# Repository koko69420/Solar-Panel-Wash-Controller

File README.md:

# Solar Panel Wash Controller

An automated, hardware-timed electronic controller PCB designed to schedule and actuate solar panel washing cycles to mitigate dust accumulation, soiling losses, and photovoltaic efficiency degradation.

Designed in KiCad with integrated Real-Time Clock (RTC) scheduling, high-current pump relay/driver stages, and industrial terminal interfaces.

---

## Features

- **Automated Cleaning Schedule**:
  - Precision timekeeping via dedicated I2C Real-Time Clock (RTC) module (DS3231/DS1307 battery-backed) for reliable daily or weekly dawn/dusk wash cycles.
- **Robust Pump & Solenoid Drive Stage**:
  - High-current relay and switching stage engineered to drive 12V/24V high-pressure water booster pumps and solenoid valves.
  - Flyback diode suppression and optocoupled logic isolation to prevent inductive transient resets.
- **Aesthetic Rounded-Track PCB Design**:
  - Custom PCB routing featuring smooth curved/teardrop trace geometry for improved signal integrity and solder-mask resilience.
  - Multi-layer power routing with broad copper pours to handle high inrush pump currents.
- **Modular Sub-System Layout**:
  - Dedicated sub-module architecture separating the low-voltage control/logic plane from the high-voltage actuator switching plane.

---

## Hardware Specification

- **RTC Module**: I2C Real-Time Clock with CR2032 backup battery holder (`RTC Module.kicad_sym`).
- **Control Interface**: Multi-pin microcontroller interface header with analog and digital telemetry pins.
- **Output Actuators**: SPDT Power Relays / High-Side Power Switching stages.
- **PCB Stackup**: 2-layer FR4 (1.6 mm core, 1 oz copper).
- **Renders & Manufacturing**:
  - 3D photorealistic board renders: `Front.png` and `Back.png`.
  - Manufacturing schematic: `Schematic.pdf` / `Schematic.png`.

---

## Hardware Renders & Schematic

### 3D Photorealistic PCB Views

| Top View | Bottom View |
| :---: | :---: |
|  |  |

### Electrical Schematic

---

## Project Structure

```text
Solar-Panel-Wash-Controller/
├── Front.png                         # 3D PCB front render
├── Back.png                          # 3D PCB back render
├── Schematic.pdf                     # Complete schematic documentation
├── Solar_pannel_wash_controller.kicad_sch # Main KiCad schematic
├── Solar_pannel_wash_controller.kicad_pcb # Main KiCad PCB layout
├── Solar_pannel_wash_controller.kicad_pro # KiCad project configuration
├── RTC Module.kicad_sym              # Custom RTC schematic symbol
├── Solar_pannel_wash_controller_sub-modules/ # Modular breakout & rounded PCB files
│   ├── Solar_pannel_wash_controller_sub-modules.kicad_sch
│   ├── Solar_pannel_wash_controller_sub-modules.kicad_pcb
│   └── Solar_pannel_wash_controller_sub-modules-rounded.kicad_pcb
├── .gitignore                        # Git ignore rules
└── README.md                         # Project documentation
```

---

## EDA & Design Files

Designed using **KiCad 7 / 8**:
- Open `Solar_pannel_wash_controller.kicad_pro` to inspect or modify the full system schematic and board layout.
- Review `Schematic.pdf` for circuit wiring, power distribution networks, and connector assignments.

---

## License

Hardware design. All rights reserved by the author.

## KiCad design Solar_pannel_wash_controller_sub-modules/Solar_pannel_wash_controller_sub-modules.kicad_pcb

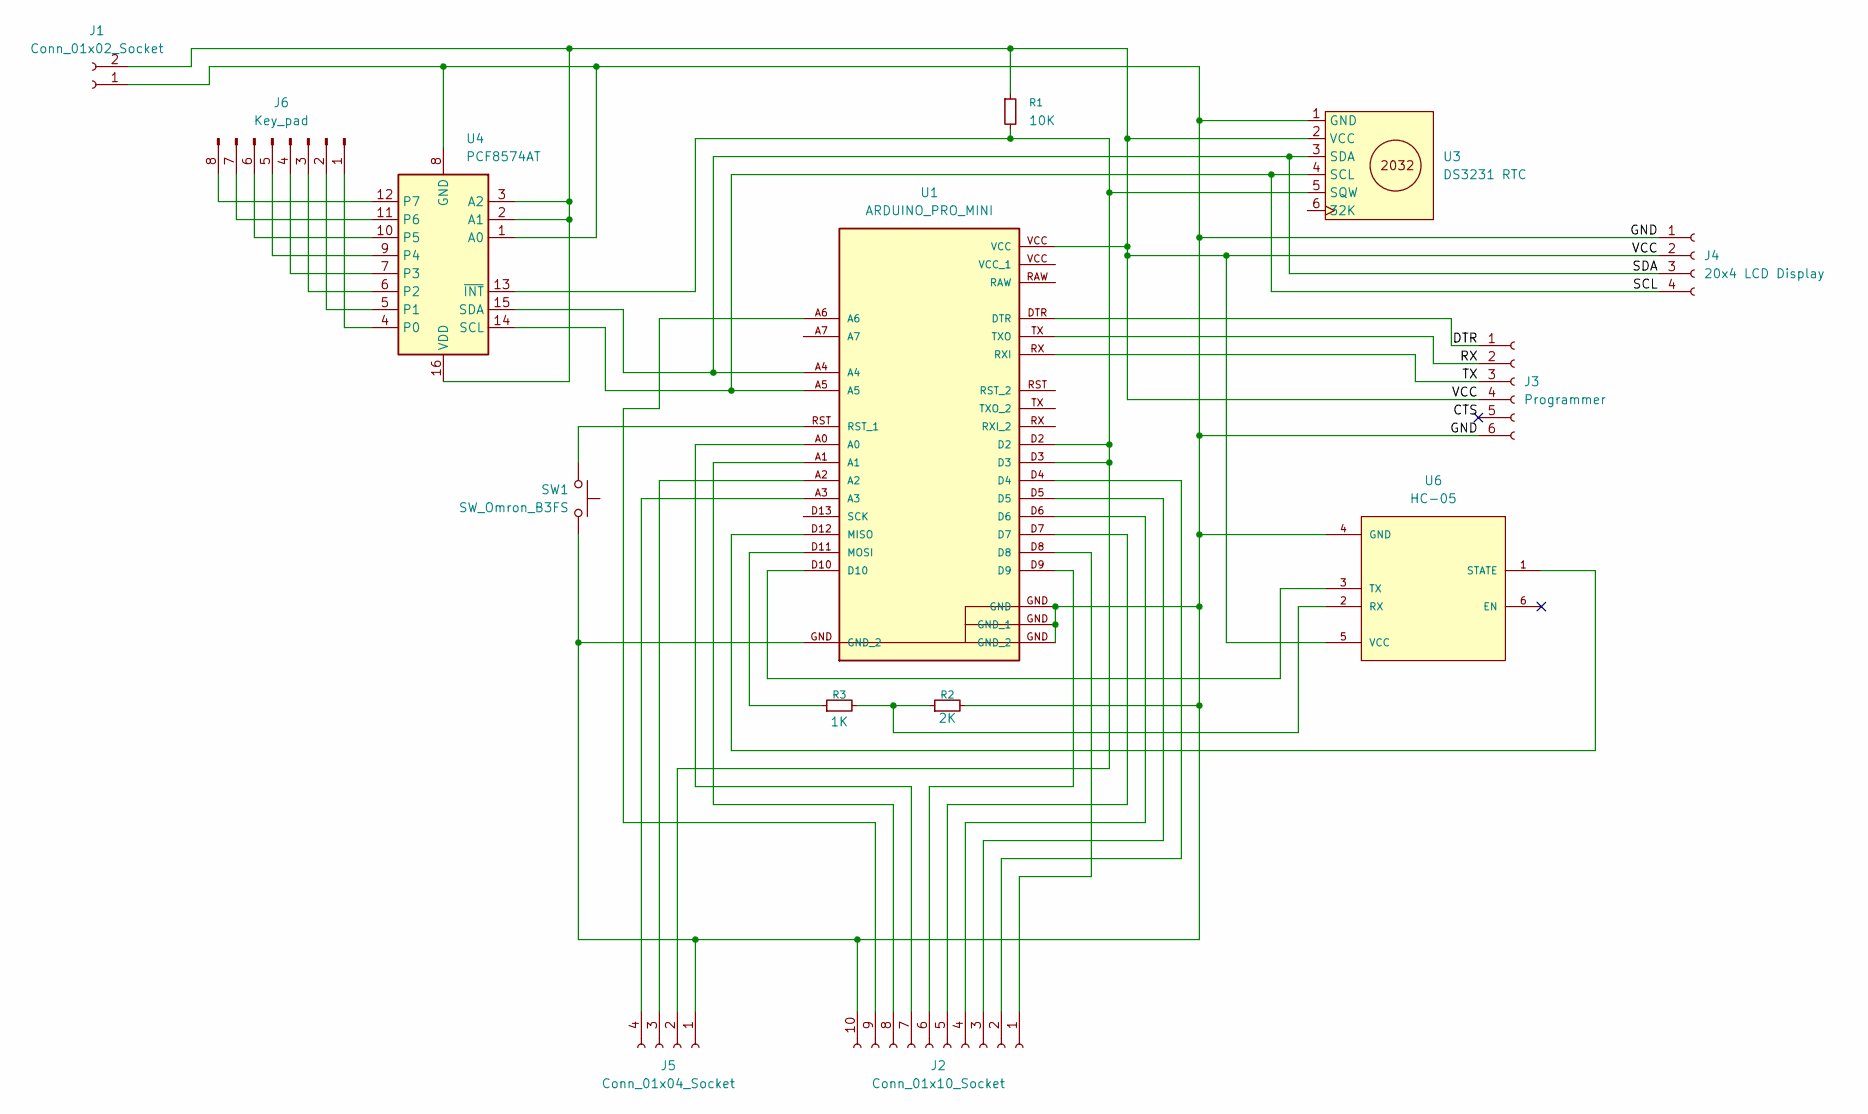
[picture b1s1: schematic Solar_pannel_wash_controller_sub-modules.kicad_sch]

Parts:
J1: Conn_01x02_Socket; JST_XH_B2B-XH-A_1x02_P2.50mm_Vertical
J2: Conn_01x10_Socket; JST_XH_B10B-XH-A_1x10_P2.50mm_Vertical
J3: Programmer; PinSocket_1x06_P2.54mm_Horizontal
J4: 20x4 LCD Display; JST_XH_B4B-XH-A_1x04_P2.50mm_Vertical
J5: Conn_01x04_Socket; JST_XH_B4B-XH-A_1x04_P2.50mm_Vertical
J6: Key_pad; PinHeader_1x08_P2.54mm_Vertical
R1: 10K; R_1206_3216Metric_Pad1.30x1.75mm_HandSolder
R2: 2K; R_1206_3216Metric_Pad1.30x1.75mm_HandSolder
R3: 1K; R_1206_3216Metric_Pad1.30x1.75mm_HandSolder
SW1: SW_Omron_B3FS; SW_SPST_Omron_B3FS-101xP
U1: ARDUINO_PRO_MINI; MODULE_ARDUINO_PRO_MINI; PARTREV N/A
U3: DS3231 RTC; DS3231_RTC_Module
U4: PCF8574AT; SOIC-16W_7.5x10.3mm_P1.27mm
U6: HC-05; HC-05_Bluetooth_Module; PARTREV N/A

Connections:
/CTS: J3.5 (CTS)
/DTR: J3.1 (DTR), U1.DTR
/RX: J3.2 (RX), U1.TX (TXO)
/SCL: J4.4 (SCL), U1.A5, U3.4 (SCL), U4.14 (SCL)
/SDA: J4.3 (SDA), U1.A4, U3.3 (SDA), U4.15 (SDA)
/TX: J3.3 (TX), U1.RX (RXI)
/VCC: J1.2, J3.4 (VCC), J4.2 (VCC), R1.1, U1.VCC, U3.2 (VCC), U4.2 (A1), U4.3 (A2), U4.16 (VDD), U6.5 (VCC)
GND: J1.1, J2.10 (GND), J3.6 (GND), J4.1 (GND), J5.1, R2.2, SW1.1, U1.GND (GND_2), U1.JP1_6 (GND), U3.1 (GND), U4.1 (A0), U4.8 (GND), U6.4 (GND); also elsewhere on the board
unnamed: J2.8 (F-Sense), U1.A1
unnamed: J2.9 (Flow), U1.A6
unnamed: J2.1 (M), U1.D8
unnamed: J2.6 (M_Sense), U1.D9
unnamed: J2.7 (S-Sense), U1.A0
unnamed: J2.2 (Z1), U1.D4
unnamed: J2.3 (Z2), U1.D5
unnamed: J2.4 (Z3), U1.D6
unnamed: J2.5 (Z4), U1.D7
unnamed: J5.2, R1.2, U1.D2, U1.D3, U3.5 (SQW), U4.13 (~INT)
unnamed: J5.3, U1.A2
unnamed: J5.4, U1.A3
unnamed: J6.1, U4.4 (P0)
unnamed: J6.2, U4.5 (P1)
unnamed: J6.3, U4.6 (P2)
unnamed: J6.4, U4.7 (P3)
unnamed: J6.5, U4.9 (P4)
unnamed: J6.6, U4.10 (P5)
unnamed: J6.7, U4.11 (P6)
unnamed: J6.8, U4.12 (P7)
unnamed: U1.D12 (MISO), U6.1 (STATE)
unnamed: R3.1, U1.D11 (MOSI)
unnamed 30: SW1.2, U1.RST (RST_1); also elsewhere on the board
unnamed: R2.1, R3.2, U6.2 (RX)
unnamed: U1.D10, U6.3 (TX)

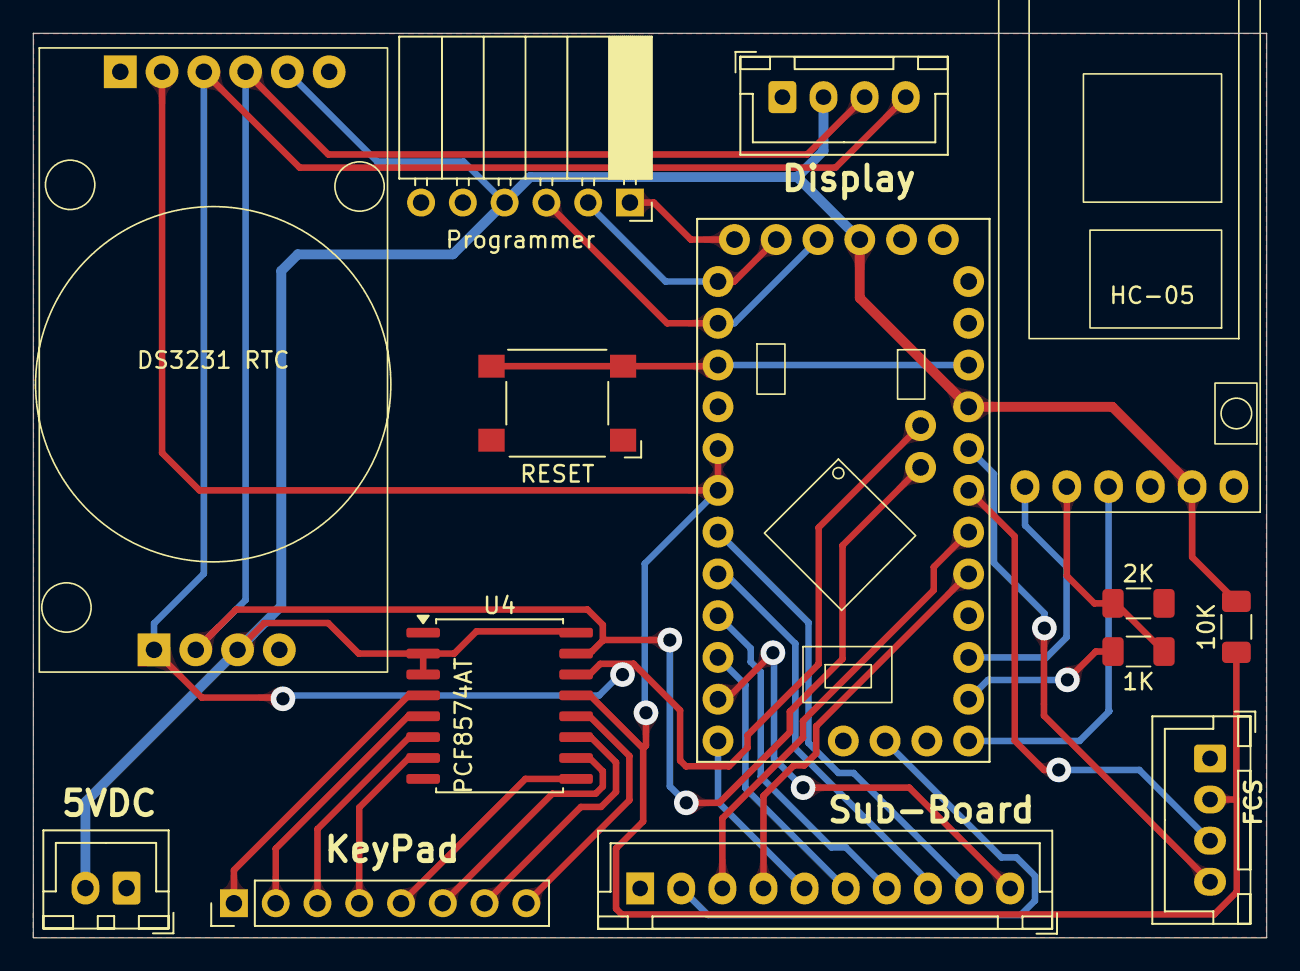
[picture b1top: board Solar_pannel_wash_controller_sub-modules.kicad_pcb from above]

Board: 2 copper layers, 75.0 x 55.0 mm, 14 parts (0 on the bottom side), 32 nets.

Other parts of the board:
RESET: SW_Omron_B3FS; SW_SPST_Omron_B3FS-101xP

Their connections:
GND: RESET.1; also elsewhere on the board
unnamed 30: RESET.2; also elsewhere on the board
